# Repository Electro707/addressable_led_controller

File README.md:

# Addressable LED Strip Controller
#### Rev 4

This is the repository for my LED strip controller. This LED controller is capable of controlling any addressable LED strip (1 or two data wires).

`Image of real PCB Rev4 coming soon!`

## Firmware

This controller uses the [WLED firmware](https://github.com/Aircoookie/WLED). Instructions to upload the firmware unto the board can be found on their webpage.

Thru J2, you can connect an ESP32 programmer such as the ESP-Prog. You can also make your own "automatic downloader" (i.e not requiring to reset the device and selecting boot mode when uploading) circuit. Details of which can be found on Espressif's ESP-Prog docs on [Automatic Downloading Function](https://espressif-docs.readthedocs-hosted.com/projects/espressif-esp-iot-solution/en/latest/hw-reference/ESP-Prog_guide.html#automatic-downloading-function).

## PI Matching Network Values

#### Rev 2

The PI Matching network values have been calculated by measuring the impedance of the antenna mounted on a bare board. As image of the setup is shown below:

The impedance was measured with my handy NanoVNA V2+4. The measured impedance at 2.45Ghz, shown below, was 21.9+5.48jΩ. Plugging those numbers into a [PI matching network calculator](https://www.eeweb.com/tools/pi-match/), we get 2.09nH for L, 2.65pF for Cs, and 3.99pF for Cl. The values have been rounded to the nearest available values that is reasonable to buy (this is RF anyways, I could have sneezed and the values would be slightly off).

#### Rev 4

At 2.45Gz, impedance was 17.5-35.8jΩ. We get 2.3194nH for L, 3.898pF for Cs, and 4.429pF for Cl.

## Rev 3 Branch-Off

Rev 3 of this project was a fully-featured POE version of this controller. I since has made this revision, which is closer to the original small design, so I decided to branch Rev3 off to it's own repo: [Electro707/addressable_led_controller_poe](https://github.com/Electro707/addressable_led_controller_poe)

## Rev 4 Design Reasonings

Over at [DesignConsiderations.md](DesignConsiderations.md), I wrote some design reasonings as to why some things are the way they are designed for Rev 4 of the board. Feel free to have a look, keep in mind they are more internal notes if anything.

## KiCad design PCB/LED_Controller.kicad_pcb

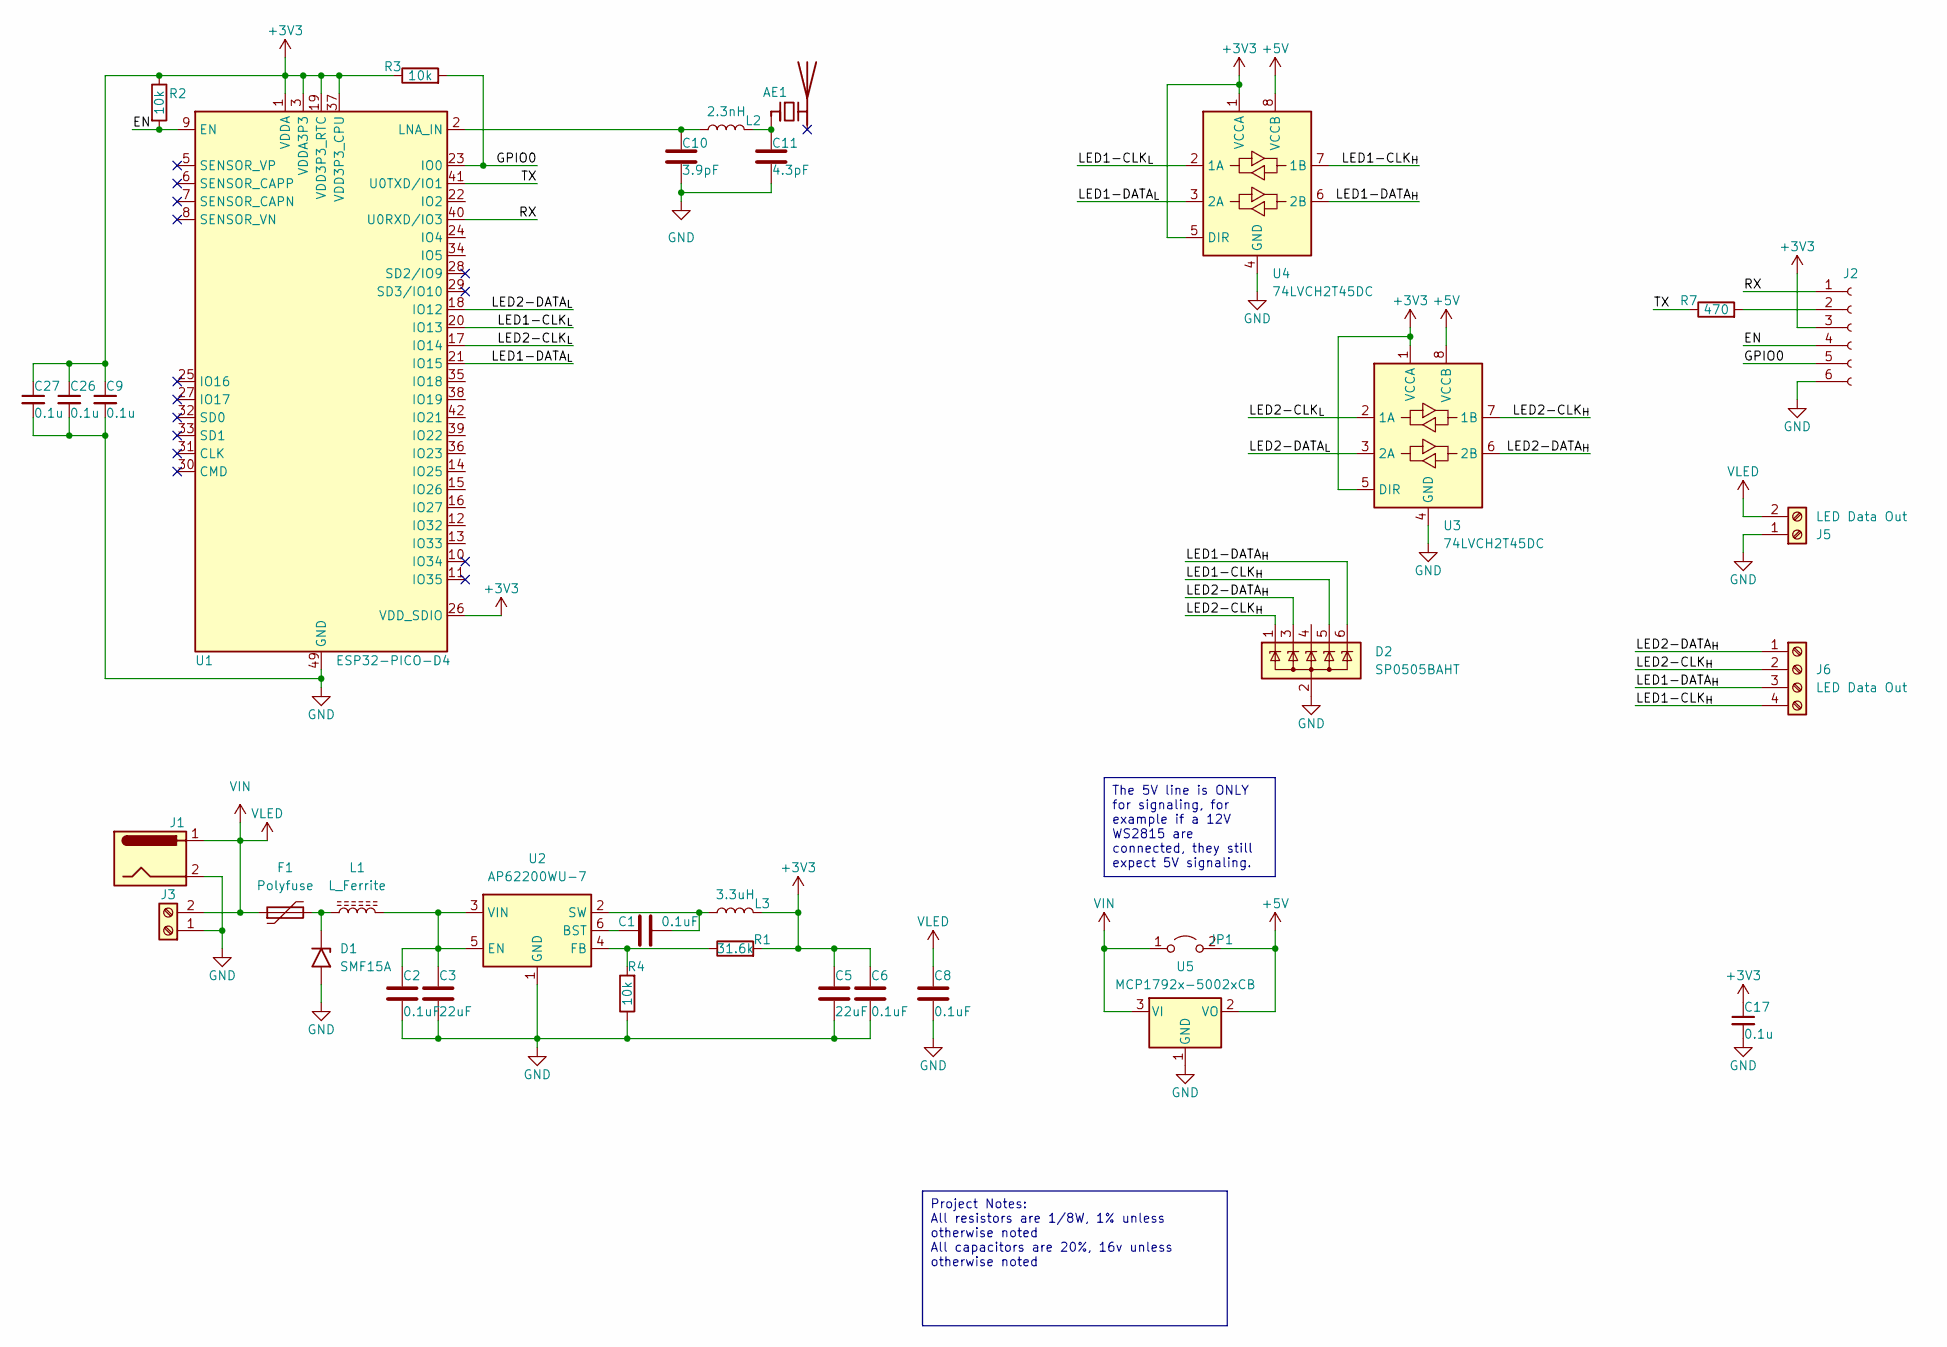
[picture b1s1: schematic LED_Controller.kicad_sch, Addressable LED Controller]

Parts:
AE1: Antenna_Chip; Johanson_2450AT43F0100
C1, C2, C6, C8: 0.1uF; C_0603_1608Metric
C3, C5: 22uF; C_1206_3216Metric_Pad1.33x1.80mm_HandSolder
C9, C17, C26, C27: 0.1u; C_0603_1608Metric
C10: 3.9pF; C_0603_1608Metric
C11: 4.3pF; C_0603_1608Metric
D1: SMF15A; D_SMF
D2: SP0505BAHT; SOT-23-6
F1: Polyfuse; Fuse_1206_3216Metric
J1: Barrel_Jack; BarrelJack_Horizontal
J2: Conn_01x06_Female; Tag-Connect_TC2030-IDC-NL_2x03_P1.27mm_Vertical
J3: Screw_Terminal_01x02; TerminalBlock_Phoenix_MKDS-1,5-2-5.08_1x02_P5.08mm_Horizont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
J5: LED Data Out; TerminalBlock_Phoenix_PT-1,5-2-3.5-H_1x02_P3.50mm_Horizontal
J6: LED Data Out; TerminalBlock_TE_282834-4_1x04_P2.54mm_Horizontal
JP1: Jumper_2_Bridged; SolderJumper-2_P1.3mm_Open_TrianglePad1.0x1.5mm
L1: L_Ferrite; L_0805_2012Metric
L2: 2.3nH; L_0603_1608Metric
L3: 3.3uH; L_1206_3216Metric_Pad1.22x1.90mm_HandSolder
R1: 31.6k; R_0805_2012Metric_Pad1.20x1.40mm_HandSolder
R2, R3: 10k; R_0603_1608Metric
R4: 10k; R_0805_2012Metric_Pad1.20x1.40mm_HandSolder
R7: 470; R_0603_1608Metric_Pad0.98x0.95mm_HandSolder
U1: ESP32-PICO-D4; QFN-48-1EP_7x7mm_P0.5mm_EP5.3x5.3mm
U2: AP62200WU-7; TSOT-23-6
U3, U4: 74LVCH2T45DC; VSSOP-8_2.3x2mm_P0.5mm
U5: MCP1792x-5002xCB; SOT-23

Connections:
+3V3: C5.1, C6.1, C9.1, C17.1, C26.1, C27.1, J2.3, L3.2, R1.2, R2.1, R3.1, U1.1 (VDDA), U1.3 (VDDA3P3), U1.4 (VDDA3P3), U1.19 (VDD3P3_RTC), U1.26 (VDD_SDIO), U1.37 (VDD3P3_CPU), U1.43 (VDDA), U1.46 (VDDA), U3.1 (VCCA), U3.5 (DIR), U4.1 (VCCA), U4.5 (DIR)
+5V: JP1.2 (B), U3.8 (VCCB), U4.8 (VCCB), U5.2 (VO)
/EN: J2.4, R2.2, U1.9 (EN)
/GPIO0: J2.5, R3.2, U1.23 (IO0)
/LED1-CLK_{H}: D2.5 (K), J6.4, U4.7 (1B)
/LED1-CLK_{L}: U1.20 (IO13), U4.2 (1A)
/LED1-DATA_{H}: D2.6 (K), J6.3, U4.6 (2B)
/LED1-DATA_{L}: U1.21 (IO15), U4.3 (2A)
/LED2-CLK_{H}: D2.1 (K), J6.2, U3.7 (1B)
/LED2-CLK_{L}: U1.17 (IO14), U3.2 (1A)
/LED2-DATA_{H}: D2.3 (K), J6.1, U3.6 (2B)
/LED2-DATA_{L}: U1.18 (IO12), U3.3 (2A)
/RX: J2.1, U1.40 (U0RXD/IO3)
/TX: R7.1, U1.41 (U0TXD/IO1)
GND: C2.2, C3.2, C5.2, C6.2, C8.2, C9.2, C10.2, C11.2, C17.2, C26.2, C27.2, D1.2 (A2), D2.2 (A), J1.2, J2.6, J3.1, J5.1, R4.1, U1.49 (GND), U2.1 (GND), U3.4 (GND), U4.4 (GND), U5.1 (GND)
unnamed: AE1.1 (FEED), C11.1, L2.2
unnamed: D1.1 (A1), F1.2, L1.1
unnamed: J2.2, R7.2
unnamed: C10.1, L2.1, U1.2 (LNA_IN)
unnamed: C1.1, U2.6 (BST)
unnamed: C2.1, C3.1, L1.2, U2.3 (VIN), U2.5 (EN)
unnamed: R1.1, R4.2, U2.4 (FB)
unnamed: C1.2, L3.1, U2.2 (SW)
VIN: C8.1, F1.1, J1.1, J3.2, J5.2, JP1.1 (A), U5.3 (VI)

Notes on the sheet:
Project Notes: All resistors are 1/8W, 1% unless otherwise noted All capacitors are 20%, 16v unless otherwise noted
The 5V line is ONLY for signaling, for example if a 12V WS2815 are connected, they still expect 5V signaling.

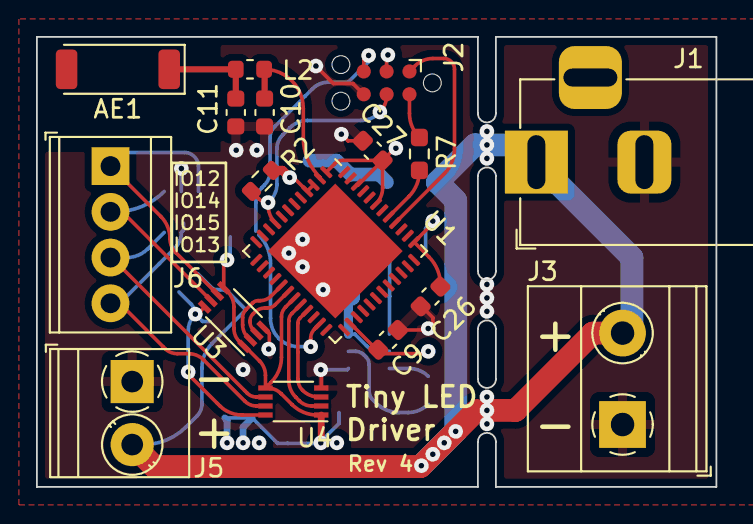
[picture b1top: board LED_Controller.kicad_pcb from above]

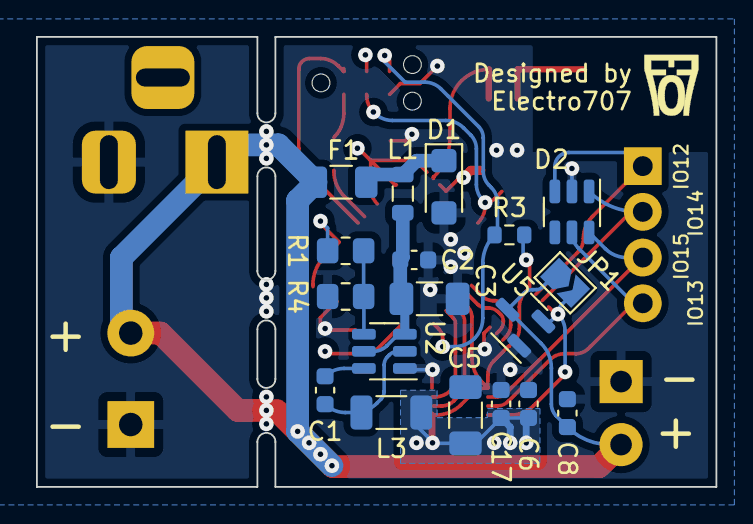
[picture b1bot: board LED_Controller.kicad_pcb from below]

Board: 4 copper layers, 37.8 x 25.0 mm, 35 parts (18 on the bottom side), 24 nets.

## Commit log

2023-06-24 Rev 1 push
2023-06-24 Rev 2.0 local push
2023-06-25 Updated README to include impedance matching calculation Updated case for screw tollerance Updated schematic to fill in values for PI network
2023-06-25 Added picture
2023-07-04 Updated CAD Drawing
2023-07-05 Added license
2023-07-05 Started work on V3 of PCB
2023-07-05 More work, added ethernet controller and ethernet pin
2023-07-05 Moved new symbol to internal library
2023-07-27 More work, including hierarchical sheets breakout
2023-07-30 Started on board layout
2023-07-31 Started serious board layout
2023-08-01 More layout work
2023-08-04 Close-to-final PCB layout, passes most routing DRC I think
2023-08-07 Almost-Almost PCB design. Minor improvements on copper layer Silkscreen cleanup schematic sheet cleanup (now with subsheet titles)
2023-08-11 Final Rev 3 board
    Many changes that are finalization changes mostly
2023-10-02 Updated schematic on repo. Added so cap have voltage rating on schematic
2023-11-19 Updated picture and README to v3
2024-09-09 Updated to Rev 4
2024-09-09 Added some design notes I had laying around
